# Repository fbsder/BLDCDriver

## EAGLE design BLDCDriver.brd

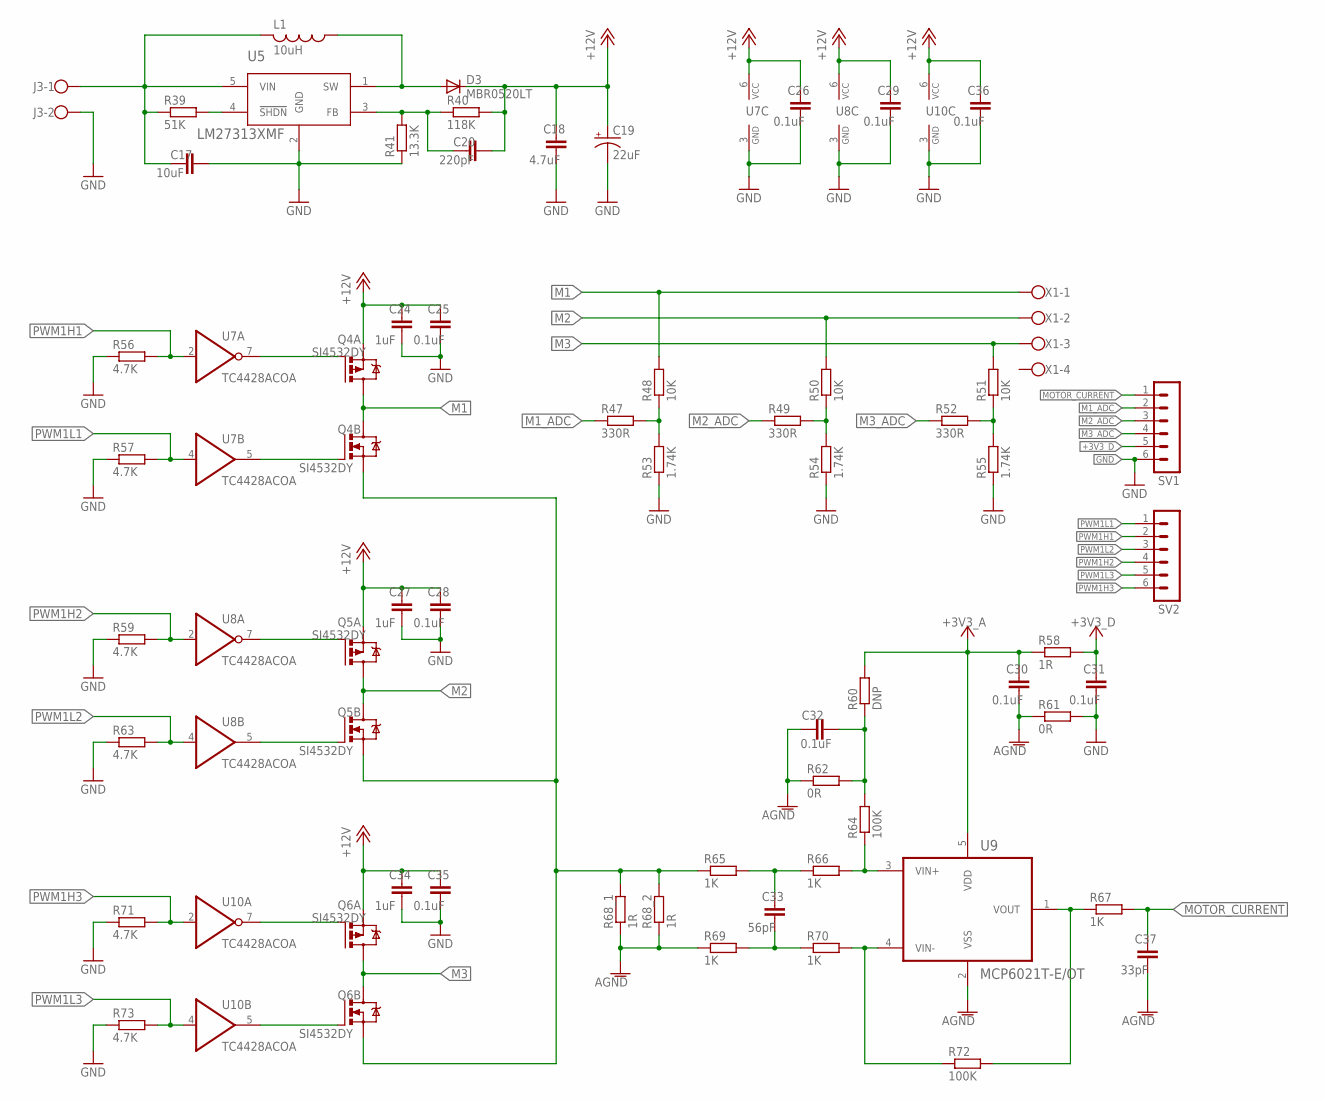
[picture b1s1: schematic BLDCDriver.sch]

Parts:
C17: 10uF; C0805
C18: 4.7uF; C0805
C19: 22uF; E2,5-6
C20: 220pF; C0805
C24, C27, C34: 1uF; C0805
C25, C26, C28, C29, C30, C31, C32, C35, C36: 0.1uF; C0805
C33: 56pF; C0805
C37: 33pF; C0805
D3: MBR0520LT; SOD123
J3: W237-102
L1: 10uH; L3225M
Q4, Q5, Q6: SI4532DY; SOIC127P600X175-8N
R39: 51K; R0805
R40: 118K; R0805
R41: 13.3K; R0805
R47, R49, R52: 330R; R0805
R48, R50, R51: 10K; R0805
R53, R54, R55: 1.74K; R0805
R56, R57, R59, R63, R71, R73: 4.7K; R0805
R58, R68_1, R68_2: 1R; R0805
R60: DNP; R0805
R61, R62: 0R; R0805
R64, R72: 100K; R0805
R65, R66, R67, R69, R70: 1K; R0805
SV1, SV2: MA06-1
U5: LM27313XMF; SOT95P285X120-5N
U7, U8, U10: TC4428ACOA; SOIC127P600X175-8N
U9: MCP6021T-E/OT; SOT95P320X145-5N
X1: W237-4

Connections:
+3V3_A: C30.1, R58.1, R60.2, U9.5 (VDD)
+3V3_D: C31.1, R58.2, SV1.5
+12V: C18.1, C19.+, C20.2, C24.2, C25.2, C26.1, C27.2, C28.2, C29.1, C34.2, C35.2, C36.1, D3.C, Q4.1 (S), Q5.1 (S), Q6.1 (S), R40.2, U7.6 (VCC), U8.6 (VCC), U10.6 (VCC)
AGND: C30.2, C32.1, C37.2, R61.1, R62.1, R68_1.1, R68_2.1, R69.1, U9.2 (VSS)
GND: C17.2, C18.2, C19.-, C24.1, C25.1, C26.2, C27.1, C28.1, C29.2, C31.2, C34.1, C35.1, C36.2, J3.2, R41.1, R53.1, R54.1, R55.1, R56.1, R57.1, R59.1, R61.2, R63.1, R71.1, R73.1, SV1.6, U5.2 (GND), U7.3 (GND), U8.3 (GND), U10.3 (GND)
M1: Q4.5 (D), Q4.7 (D), R48.2, X1.1
M1_ADC: R47.1, SV1.2
M2: Q5.5 (D), Q5.7 (D), R50.2, X1.2
M2_ADC: R49.1, SV1.3
M3: Q6.5 (D), Q6.7 (D), R51.2, X1.3
M3_ADC: R52.1, SV1.4
MOTOR_CURRENT: C37.1, R67.2, SV1.1
unnamed: C17.1, J3.1, L1.2, R39.1, U5.5 (VIN)
unnamed: R39.2, U5.4 (!SHDN!)
unnamed: Q6.4 (G), U10.5 (O)
unnamed: C20.1, R40.1, R41.2, U5.3 (FB)
unnamed: D3.A, L1.1, U5.1 (SW)
unnamed: Q6.2 (G), U10.7 (O)
unnamed: Q5.4 (G), U8.5 (O)
unnamed: Q5.2 (G), U8.7 (O)
unnamed: Q4.4 (G), U7.5 (O)
unnamed: Q4.2 (G), U7.7 (O)
unnamed: C33.2, R65.2, R66.1
unnamed: C33.1, R69.2, R70.1
unnamed: R64.1, R66.2, U9.3 (VIN+)
unnamed: Q4.3 (S), Q5.3 (S), Q6.3 (S), R65.1, R68_1.2, R68_2.2
unnamed: R70.2, R72.1, U9.4 (VIN-)
unnamed: R67.1, R72.2, U9.1 (VOUT)
unnamed: C32.2, R60.1, R62.2, R64.2
unnamed: R51.1, R52.2, R55.2
unnamed: R49.2, R50.1, R54.2
unnamed: R47.2, R48.1, R53.2
PWM1H1: R56.2, SV2.2, U7.2 (I)
PWM1H2: R59.2, SV2.4, U8.2 (I)
PWM1H3: R71.2, SV2.6, U10.2 (I)
PWM1L1: R57.2, SV2.1, U7.4 (I)
PWM1L2: R63.2, SV2.3, U8.4 (I)
PWM1L3: R73.2, SV2.5, U10.4 (I)

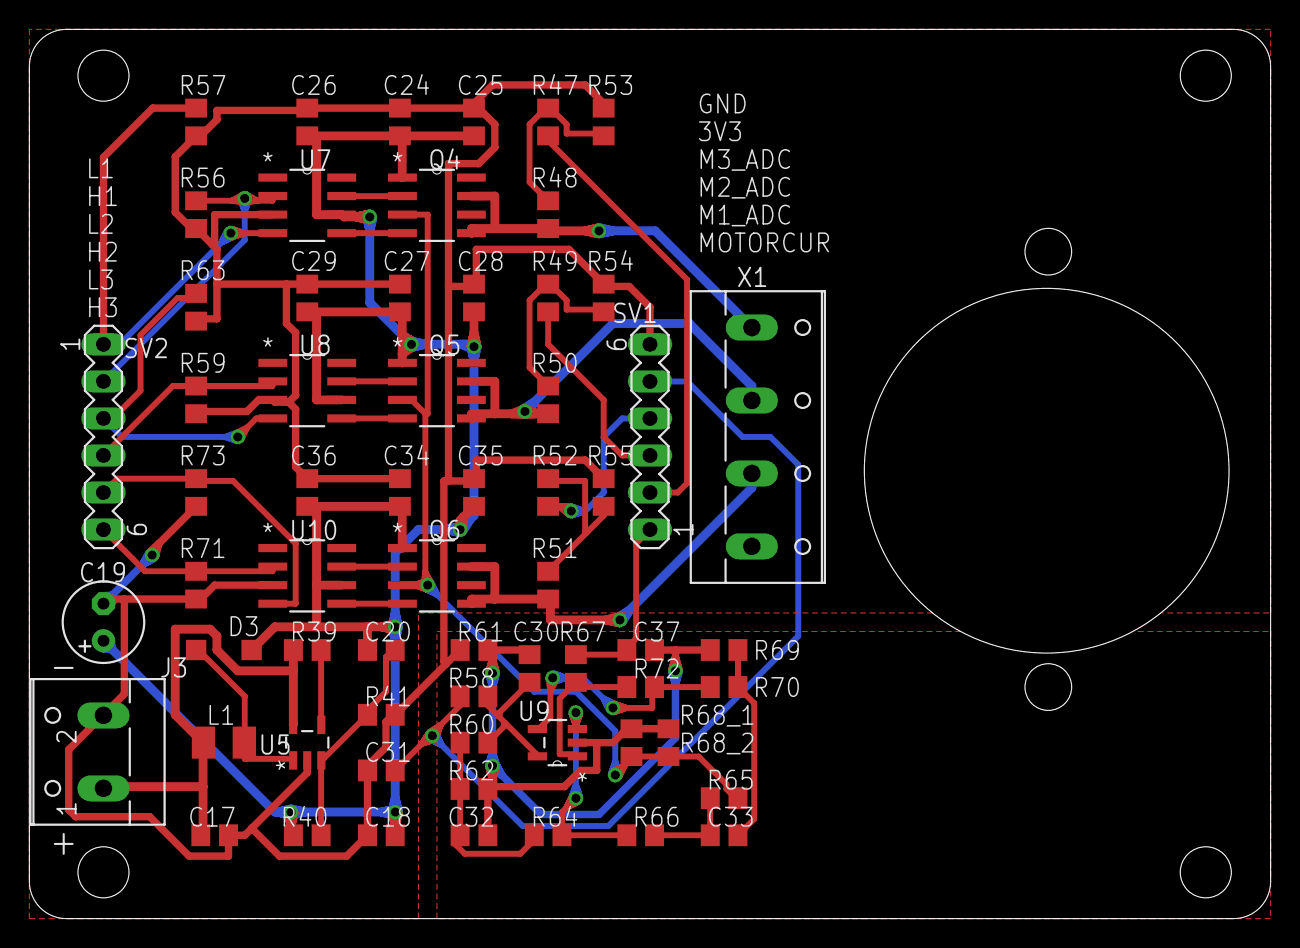
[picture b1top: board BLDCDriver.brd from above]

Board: 2 copper layers, 85.1 x 61.0 mm, 63 parts (0 on the bottom side), 38 nets.
